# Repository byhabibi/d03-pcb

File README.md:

# D03 — roaster control PCBs

Two PCBs for a 3 kg LPG drum roaster. This repo is the board design: schematic, KiCad, BOM, and fab notes. The machine firmware lives elsewhere. The later gas machine in this series is [Orion 05](https://github.com/byhabibi/orion-05). The electric sibling, including its firmware, is [D01E](https://github.com/byhabibi/d01e-roaster).

## Machine the boards serve

| Item | Value |
|---|---|
| Fuel | LPG, two solenoids |
| Power | 220 V, single phase, 50 Hz |
| Batch | 3 kg |
| HMI | Nextion NX8048K070 |
| Drum | VFD |
| Burner | servo on the gas valve |
| Thermocouples | three MAX31856 breakouts |

## Boards

| Board | KiCad | Role |
|---|---|---|
| PCB-01 MAIN-CTRL | `KiCad_LIVE_PRE_ROUTE/D03-MAIN-CTRL/` | ESP32-DevKitC seat, fixed 5 V buck, three thermocouple seats, HMI and logic |
| PCB-02 IO-PWR | `KiCad_LIVE_PRE_ROUTE/D03-IO-PWR/` | 24 V contactors, gas path, power distribution |

Open `D03-MAIN-CTRL.kicad_pro` and `D03-IO-PWR.kicad_pro`. Custom footprints are in each project's `D03.pretty` (DevKit, MP1584 module, MAX31856 breakout, contactor, SSR, fuse, PSU).

Drawings for review, without KiCad, are in `schematics/`. Start at `schematics/INDEX.html`. BOM lock is `BOM/D03_BOM_Production.csv`.

Target stack once a clean Gerber exists: 2-layer FR4, 1.6 mm, 1 oz copper, green mask, white silk.

## Do not fabricate the Gerbers in this snapshot

`PCB-01_MAIN-CTRL/Gerbers/` and `PCB-02_IO-PWR/Gerbers/` are placeholders. Both folders still carry a do-not-fab note. The KiCad projects are the pre-route seat lock: modules are placed and nets match the BOM, and the copper still has to be finished and pass DRC before a new Gerber export.

Seat lock used here:

- U1 = ESP32-DevKitC module, USB toward the top
- U3 = MP1584 fixed 5 V module, not a trimpot buck
- U4, U5, U6 = MAX31856 breakout modules
- Onboard USB-UART and its connector are do-not-place. Flash through the DevKit USB port

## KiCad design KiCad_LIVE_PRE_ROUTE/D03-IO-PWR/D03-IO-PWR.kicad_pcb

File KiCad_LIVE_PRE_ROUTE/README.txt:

D03 KiCad LIVE — PRE-ROUTE (Fase 1 seats locked)
Tanggal sync: 2026-07-20

STATUS: GO ROUTE — seats + pad-nets tally BOM / wiring / firmware
  (lihat ../PRE_ROUTE_SENIOR_EE_GATE_BOM_WIRING_FW_2026-07-20.txt)

BUKA
----
  D03-MAIN-CTRL/D03-MAIN-CTRL.kicad_pro
  D03-IO-PWR/D03-IO-PWR.kicad_pro

SEAT LOCK
---------
  U1 = MODULE_ESP32_DEVKITC (USB = atas / -Y)
  U3 = MODULE_MP1584_4P FIXED 5V
  U4/U5/U6 = MODULE_MAX31856_8P
  J_H1 = 2x16 · U12/U13 MCP4725 · U22 PCF8591
  U8 + J_USB = DNP
  MAIN outline ~160x115 mm · tracks MAIN cleared for fresh route

JANGAN
------
  Update PCB from Schematic (schematic may lag)
  Fab dari folder Gerbers/ di atas — itu set STALE (DO_NOT_FAB)

Setelah route + DRC 0: export Gerber baru, timpa PCB-01/PCB-02 Gerbers, hapus DO_NOT_FAB.

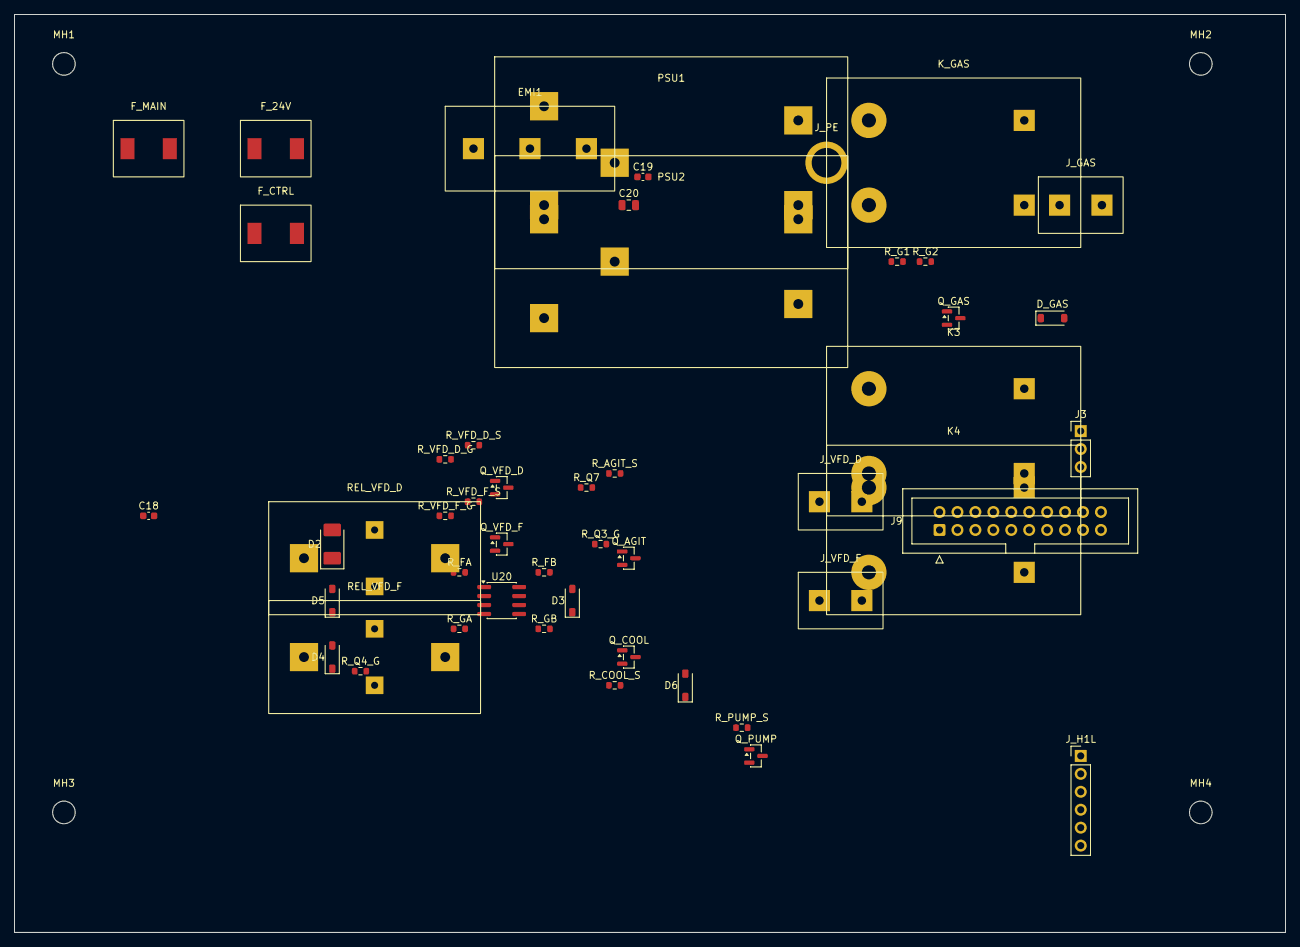
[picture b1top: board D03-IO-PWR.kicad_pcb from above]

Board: 2 copper layers, 180.0 x 130.0 mm, 54 parts (0 on the bottom side), 27 nets, no tracks yet.

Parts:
C18, C19: 100nF; C_0603_1608Metric
C20: 10uF; C_0805_2012Metric
D2: SS34; D_SMA
D3, D4, D5, D6: 1N5819; D_SOD-123
D_GAS: 1N4007; D_SOD-123
EMI1: FN2090; BLOCK_EMI
F_24V: Glass 4A; BLOCK_FUSE
F_CTRL: MCB C6 ctrl; BLOCK_FUSE
F_MAIN: MCB C32; BLOCK_FUSE
J3: Agitator; PinHeader_1x03_P2.54mm_Vertical
J9: IDC 2x10; IDC-Header_2x10_P2.54mm_Vertical
J_GAS: Gas AC out; BLOCK_TERM
J_H1L: H1L lamps 1x6; PinHeader_1x06_P2.54mm_Vertical
J_PE: PE M4; BLOCK_PE
J_VFD_D: VFD1 AI/GND; BLOCK_TERM
J_VFD_F: VFD2 AI/GND; BLOCK_TERM
K3: LC1D09BD agit; BLOCK_CONTACTOR
K4: LC1D09BD cool; BLOCK_CONTACTOR
K_GAS: LC1D09BD gas; BLOCK_CONTACTOR
MH1, MH2, MH3, MH4: M3; MountingHole_3.2mm_M3
PSU1: HDR-100-24; BLOCK_PSU
PSU2: LRS-35-12; BLOCK_PSU
Q_AGIT: AO3400; SOT-23
Q_COOL: AO3400; SOT-23
Q_GAS: AO3400; SOT-23
Q_PUMP: AO3400; SOT-23
Q_VFD_D: AO3400 VFD_D; SOT-23
Q_VFD_F: AO3400 VFD_F; SOT-23
REL_VFD_D: G5V VFD_D; BLOCK_SSR
REL_VFD_F: G5V VFD_F; BLOCK_SSR
R_AGIT_S: 1k; R_0603_1608Metric
R_COOL_S: 1k; R_0603_1608Metric
R_FA: 20k; R_0603_1608Metric
R_FB: 20k; R_0603_1608Metric
R_G1: 1k; R_0603_1608Metric
R_G2: 10k; R_0603_1608Metric
R_GA: 10k; R_0603_1608Metric
R_GB: 10k; R_0603_1608Metric
R_PUMP_S: 1k; R_0603_1608Metric
R_Q3_G, R_Q4_G: 10k; R_0603_1608Metric
R_Q7: 4.7k; R_0603_1608Metric
R_VFD_D_G: 10k; R_0603_1608Metric
R_VFD_D_S: 1k; R_0603_1608Metric
R_VFD_F_G: 10k; R_0603_1608Metric
R_VFD_F_S: 1k; R_0603_1608Metric
U20: LM358; SOIC-8_3.9x4.9mm_P1.27mm

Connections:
+12V_AUX: D4.1, J_H1L.1, PSU2.+12V, U20.8
+24V_BUS: C18.1, C19.1, C20.1, D2.1, D3.1, D5.1, D6.1, D_GAS.1, F_24V.1, F_24V.2, F_CTRL.1, F_CTRL.2, J9.1, K3.COIL+, K4.COIL+, K_GAS.COIL+, PSU1.+12V, REL_VFD_D.CTRL+, REL_VFD_F.CTRL+
AC_N: EMI1.N, PSU1.AC_N, PSU2.AC_N
AGIT_EN: D3.2, J9.8, K3.COIL-, Q_AGIT.3, R_AGIT_S.1
COOL_FAN_EN: D6.2, J9.9, K4.COIL-, Q_COOL.3, R_COOL_S.1
DAC_D_OUT: J9.11, U20.3
DAC_F_OUT: J9.12, U20.5
GAS_EN: J9.5, R_G1.1
GATE_AGIT: Q_AGIT.1, R_AGIT_S.2, R_Q3_G.1
GATE_COOL: Q_COOL.1, R_COOL_S.2, R_Q7.1
GATE_GAS: Q_GAS.1, R_G1.2, R_G2.1
GATE_PUMP: Q_PUMP.1, R_PUMP_S.2, R_Q4_G.1
GATE_VFD_D: Q_VFD_D.1, R_VFD_D_G.1, R_VFD_D_S.2
GATE_VFD_F: Q_VFD_F.1, R_VFD_F_G.1, R_VFD_F_S.2
GND: C18.2, C19.2, C20.2, J3.1, J3.2, J3.3, J9.2, J9.4, J_H1L.6, J_VFD_D.2, J_VFD_F.2, PSU1.GND, PSU2.GND, Q_AGIT.2, Q_COOL.2, Q_GAS.2, Q_PUMP.2, Q_VFD_D.2, Q_VFD_F.2, R_G2.2, R_GA.2, R_GB.2, R_Q3_G.2, R_Q4_G.2, R_Q7.2, R_VFD_D_G.2, R_VFD_F_G.2, U20.4
K_GAS_COIL+: D_GAS.2, K_GAS.COIL-, Q_GAS.3
L_GAS: J_GAS.1, K3.A1, K3.A2, K4.A1, K4.A2, K_GAS.A1, K_GAS.A2
L_MAINS: EMI1.L, F_MAIN.1, F_MAIN.2, PSU1.AC_L, PSU2.AC_L
NC: J9.3, J9.14, J9.15, J9.16, J9.17, J9.18, J9.19, J9.20, J_H1L.2, J_H1L.3, J_H1L.4, J_H1L.5
PE: EMI1.PE, J_PE.PE, PSU1.PE, PSU2.PE
PUMP_EN: D4.2, J9.10, Q_PUMP.3, R_PUMP_S.1
U20_INA_N: R_FA.2, R_GA.1, U20.2
U20_INB_N: R_FB.2, R_GB.1, U20.6
VFD1_AI: J_VFD_D.1, R_FA.1, U20.1
VFD2_AI: J_VFD_F.1, R_FB.1, U20.7
VFD_D_RUN: D2.2, J9.6, Q_VFD_D.3, REL_VFD_D.CTRL-, R_VFD_D_S.1
VFD_F_RUN: D5.2, J9.7, Q_VFD_F.3, REL_VFD_F.CTRL-, R_VFD_F_S.1

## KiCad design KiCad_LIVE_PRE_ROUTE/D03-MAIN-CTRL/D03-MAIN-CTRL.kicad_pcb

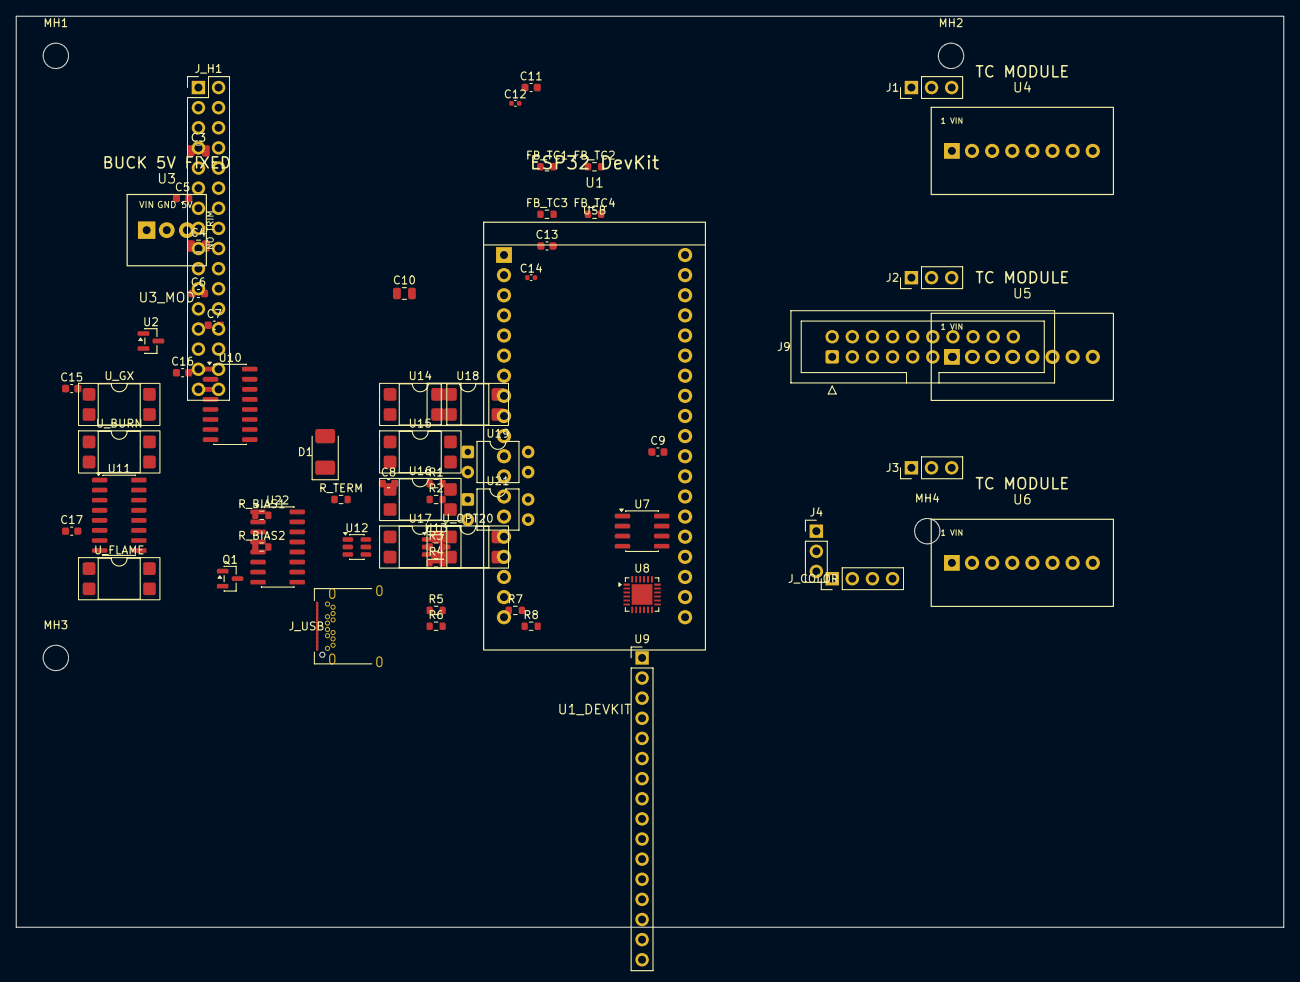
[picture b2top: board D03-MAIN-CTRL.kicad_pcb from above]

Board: 2 copper layers, 160.0 x 115.0 mm, 69 parts (0 on the bottom side), 51 nets, no tracks yet.

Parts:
C3, C4, C10: 10uF; C_0805_2012Metric
C5, C6, C7, C8, C9, C11, C13, C15, C16, C17: 100nF; C_0603_1608Metric
C12, C14: 100pF; C_0402_1005Metric
D1: SMAJ6.5CA; D_SMA
FB_TC1, FB_TC2, FB_TC3, FB_TC4: FB; R_0603_1608Metric
J1: PCC-SMP-K Bean; PinHeader_1x03_P2.54mm_Vertical
J2: PCC-SMP-K Env; PinHeader_1x03_P2.54mm_Vertical
J3: PCC-SMP-K Motor; PinHeader_1x03_P2.54mm_Vertical
J4: RS485 3p; PinHeader_1x03_P2.54mm_Vertical
J9: IDC 2x10; IDC-Header_2x10_P2.54mm_Vertical
J_COLOR: Color DNP; PinHeader_1x04_P2.54mm_Vertical
J_H1: H1 2x16; PinHeader_2x16_P2.54mm_Vertical
J_USB: USB-C; USB_C_Receptacle_Amphenol_12401548E4-2A
MH1, MH2, MH3, MH4: M3; MountingHole_3.2mm_M3
Q1: BC847C; SOT-23
R1, R3, R5, R7: 4k7; R_0603_1608Metric
R2, R4, R6, R8: 10k; R_0603_1608Metric
R_BIAS1, R_BIAS2: 560R; R_0603_1608Metric
R_TERM: 120R; R_0603_1608Metric
U1: ESP32-DevKitC-32E; MODULE_ESP32_DEVKITC
U2: MCP1700-3302E; SOT-23
U3: MP1584 FIXED 5V; MODULE_MP1584_4P
U4: MAX31856 Bean; MODULE_MAX31856_8P
U5: MAX31856 Env; MODULE_MAX31856_8P
U6: MAX31856 Motor; MODULE_MAX31856_8P
U7: MAX3485ESA+; SOIC-8_3.9x4.9mm_P1.27mm
U8: CP2102N-A02; QFN-24-1EP_4x4mm_P0.5mm_EP2.6x2.6mm
U9: DFPlayer Mini; PinHeader_1x16_P2.54mm_Vertical
U10: PCF8574AP @0x20; SOIC-16_3.9x9.9mm_P1.27mm
U11: PCF8574AP @0x21; SOIC-16_3.9x9.9mm_P1.27mm
U12: MCP4725 @0x60; SOT-23-6
U13: MCP4725 @0x61; SOT-23-6
U14, U15, U16, U17, U18: PC817C; DIP-4_W7.62mm_SMDSocket_SmallPads
U19, U21: PC817 spare; DIP-4_W7.62mm
U22: PCF8591 @0x48; SOIC-16_3.9x9.9mm_P1.27mm
U_BURN: PC817C; DIP-4_W7.62mm_SMDSocket_SmallPads
U_FLAME: PC817C; DIP-4_W7.62mm_SMDSocket_SmallPads
U_GX: PC817C; DIP-4_W7.62mm_SMDSocket_SmallPads
U_OPT20: PC817 spare (was U20); DIP-4_W7.62mm_SMDSocket_SmallPads

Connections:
+3V3_ANA: C11.1, C12.1, C13.1, C14.1, FB_TC1.1, FB_TC1.2, FB_TC2.1, FB_TC2.2, FB_TC3.1, FB_TC3.2, FB_TC4.1, FB_TC4.2, J_H1.13, U2.2, U4.1, U5.1, U6.1, U7.8, U22.14
+5V_SYS: C4.1, C5.1, C6.1, C7.1, C8.1, C9.1, C10.1, C15.1, C16.1, C17.1, J9.13, J_H1.15, J_H1.22, J_H1.25, J_USB.A4, J_USB.A9, J_USB.B4, J_USB.B9, R1.2, R3.2, R5.2, R7.2, R_BIAS1.1, R_BIAS2.1, U1.L19, U2.3, U3.3, U8.7, U8.8, U8.9, U9.1, U10.16, U11.16, U12.3, U13.3, U13.6, U14.1, U15.1, U16.1, U17.1, U18.1, U19.1, U21.1, U22.16, U_BURN.1, U_FLAME.1, U_GX.1, U_OPT20.1
+24V_IN: C3.1, J9.1, J_H1.2, U3.1
AGIT_EN: J9.8, U10.4
BTN_AIR: J_H1.4, R5.1, R6.1, U1.L9, U14.2
BTN_BURNER: J_H1.6, R3.1, R4.1, U1.L11, U16.2
BTN_COOL: J_H1.7, U11.6, U17.2
BTN_DRUM: J_H1.5, R1.1, R2.1, U1.L10, U15.2
BTN_PUMP: J_H1.8, U11.5, U18.2
BURNER_FB: U11.3, U_BURN.2
COOL_FAN_EN: J9.9, U10.5
DAC_D_OUT: J9.11, U12.1
DAC_F_OUT: J9.12, U13.1
DFPLAYER_TX: U1.R13, U9.2
ESTOP_SENSE: J_H1.9, R7.1, R8.1, U11.2
FLAME_FB: U11.4, U_FLAME.2
GAS_EN: J9.5, U10.1
GAS_PRESS: J_H1.23, U1.L5
GND: C3.2, C4.2, C5.2, C6.2, C7.2, C8.2, C9.2, C10.2, C11.2, C12.2, C13.2, C14.2, C15.2, C16.2, C17.2, D1.2, J1.1, J1.2, J1.3, J2.1, J2.2, J2.3, J3.1, J3.2, J3.3, J4.3, J9.2, J9.4, J_H1.3, J_H1.14, J_H1.16, J_H1.21, J_H1.24, J_H1.27, J_USB.A1, J_USB.A5, J_USB.A12, J_USB.B1, J_USB.B5, J_USB.B12, J_USB.SH, Q1.2, R2.2, R4.2, R6.2, R8.2, U1.L14, U1.R1, U1.R7, U2.1, U3.2, U4.3, U5.3, U6.3, U7.5, U8.10, U8.11, U8.25, U9.7, U10.8, U11.8, U12.2, U12.6, U13.2, U14.3, U14.4, U15.3, U15.4, U16.3, U16.4, U17.3, U17.4, U18.3, U18.4, U19.3, U19.4, U21.3, U21.4, U22.5, U22.6, U22.7, U22.8, U22.13, U_BURN.3, U_BURN.4, U_FLAME.3, U_FLAME.4, U_GX.3, U_GX.4, U_OPT20.3, U_OPT20.4
GX103_ILOCK: U11.1, U_GX.2
I2C_SCL: U1.R3, U10.10, U11.10, U12.5, U13.5, U22.10
I2C_SDA: U1.R6, U10.9, U11.9, U12.4, U13.4, U22.9
MQ6_ADC: J_H1.26, U1.L6
NC: J9.3, J9.14, J9.15, J9.16, J9.17, J9.18, J9.19, J9.20, J_COLOR.1, J_COLOR.2, J_COLOR.3, J_COLOR.4, J_H1.31, J_H1.32, J_USB.A2, J_USB.A3, J_USB.A8, J_USB.A10, J_USB.A11, J_USB.B2, J_USB.B3, J_USB.B8, J_USB.B10, J_USB.B11, U1.L1, U1.L2, U1.L13, U1.L16, U1.L17, U1.L18, U1.R15, U1.R17, U1.R18, U1.R19, U4.2, U4.8, U5.2, U5.8, U6.2, U6.8, U8.1, U8.2, U8.3, U8.4, U8.12, U8.13, U8.16, U8.17, U8.18, U8.19, U8.20, U8.21, U8.22, U8.23, U8.24, U9.3, U9.4, U9.5, U9.9, U9.10, U9.11, U9.12, U9.13, U9.14, U9.15, U9.16, U10.11, U10.12, U10.13, U10.14, U10.15, U11.7, U11.11, U11.12, U11.13, U11.14, U11.15, U19.2, U21.2, U22.2, U22.3, U22.4, U22.11, U22.12, U22.15, U_OPT20.2
POT_AIR: J_H1.10, U1.L3
POT_BURN: J_H1.11, U1.L4
POT_DRUM: J_H1.12, U22.1
PROX_RPM: J_H1.1, U1.L12
PUMP_EN: J9.10, U10.6
RS485_A: D1.1, J4.1, J_H1.19, R_BIAS1.2, R_TERM.1, U7.6
RS485_B: J4.2, J_H1.20, R_BIAS2.2, R_TERM.2, U7.7
RS485_DE: Q1.1, U10.7
RS485_DE_n: Q1.3, U7.2, U7.3
SPI_CS_BEAN: U1.R10, U4.5
SPI_CS_ENV: U1.R16, U5.5
SPI_CS_MOTOR: U1.R14, U6.5
SPI_MISO: U1.R8, U4.4, U5.4, U6.4
SPI_MOSI: U1.R2, U4.7, U5.7, U6.7
SPI_SCK: U1.R9, U4.6, U5.6, U6.6
SPK_N: J_H1.30, U9.8
SPK_P: J_H1.29, U9.6
UART0_RX: U1.R5, U8.5
UART0_TX: U1.R4, U8.6
UART1_RX: U1.R12, U7.1
UART1_TX: U1.R11, U7.4
UART2_RX: J_H1.17, U1.L7
UART2_TX: J_H1.18, U1.L8
USB_DM: J_USB.A7, J_USB.B7, U8.15
USB_DP: J_USB.A6, J_USB.B6, U8.14
VFD_D_RUN: J9.6, U10.2
VFD_F_RUN: J9.7, U10.3
